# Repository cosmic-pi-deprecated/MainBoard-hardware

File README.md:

# MainBoard-hardware
Mainboard for Arduino DUE based versions

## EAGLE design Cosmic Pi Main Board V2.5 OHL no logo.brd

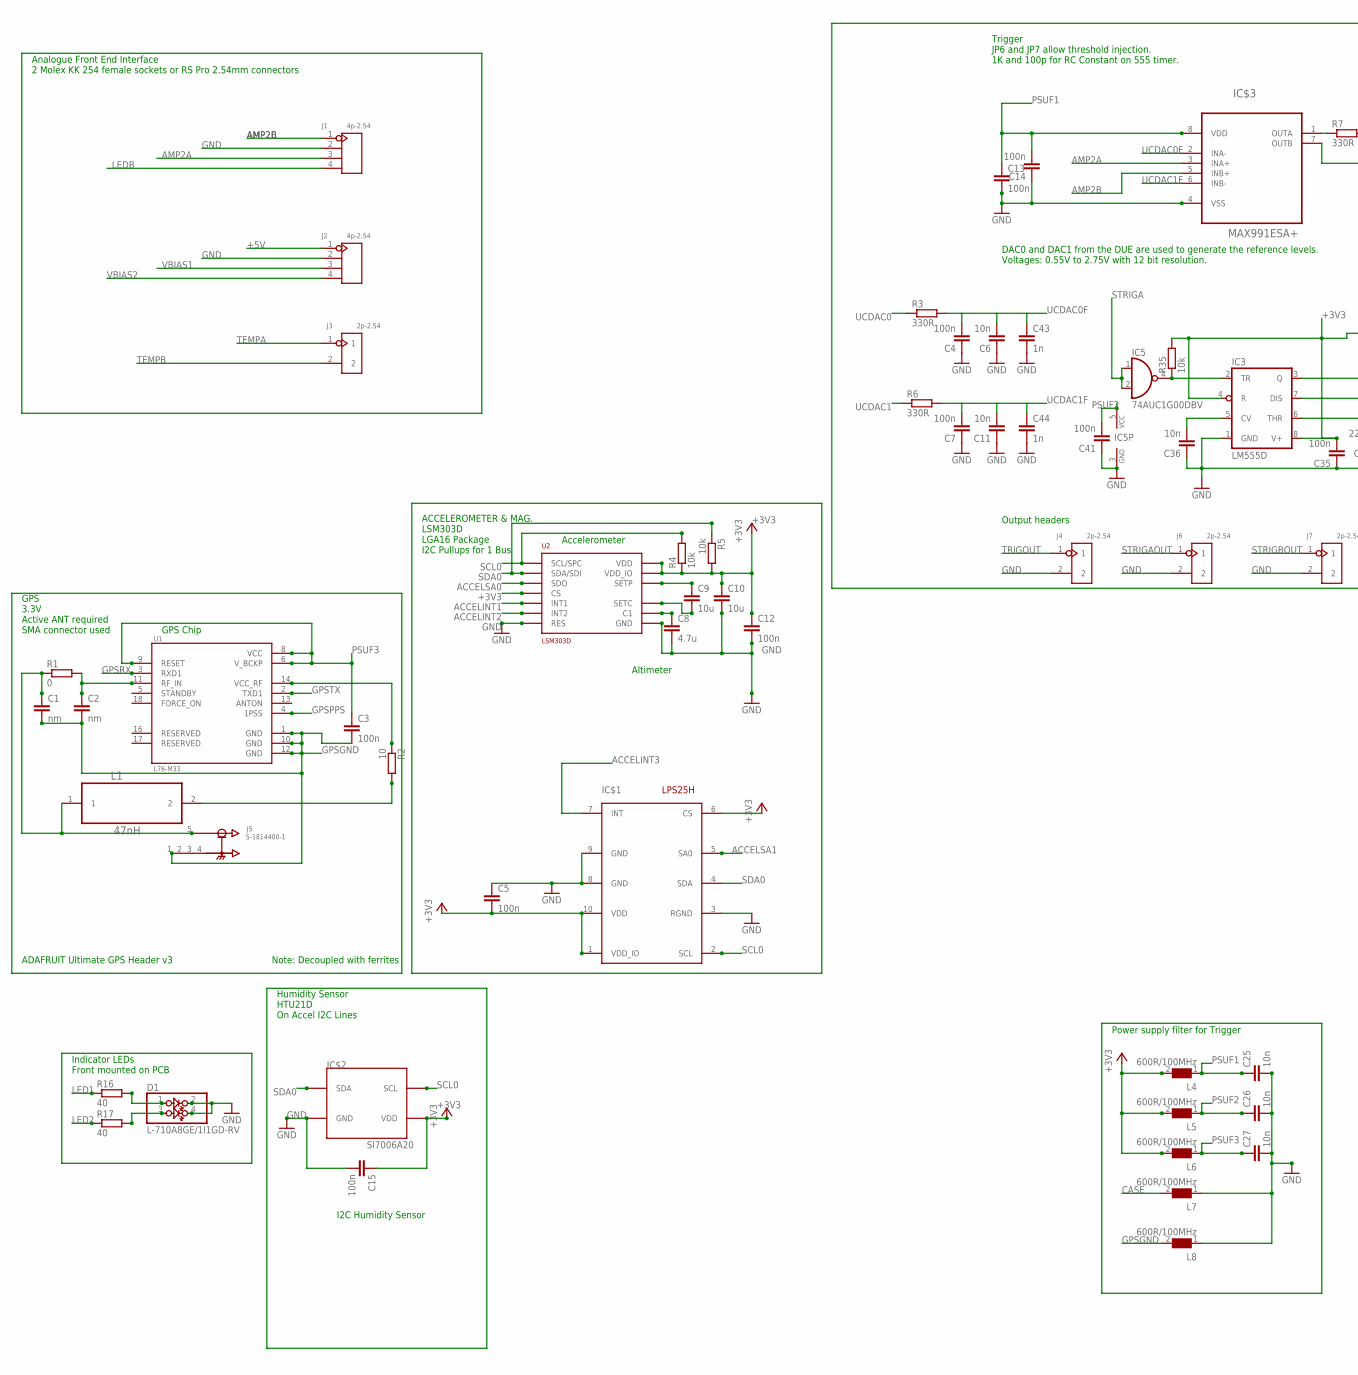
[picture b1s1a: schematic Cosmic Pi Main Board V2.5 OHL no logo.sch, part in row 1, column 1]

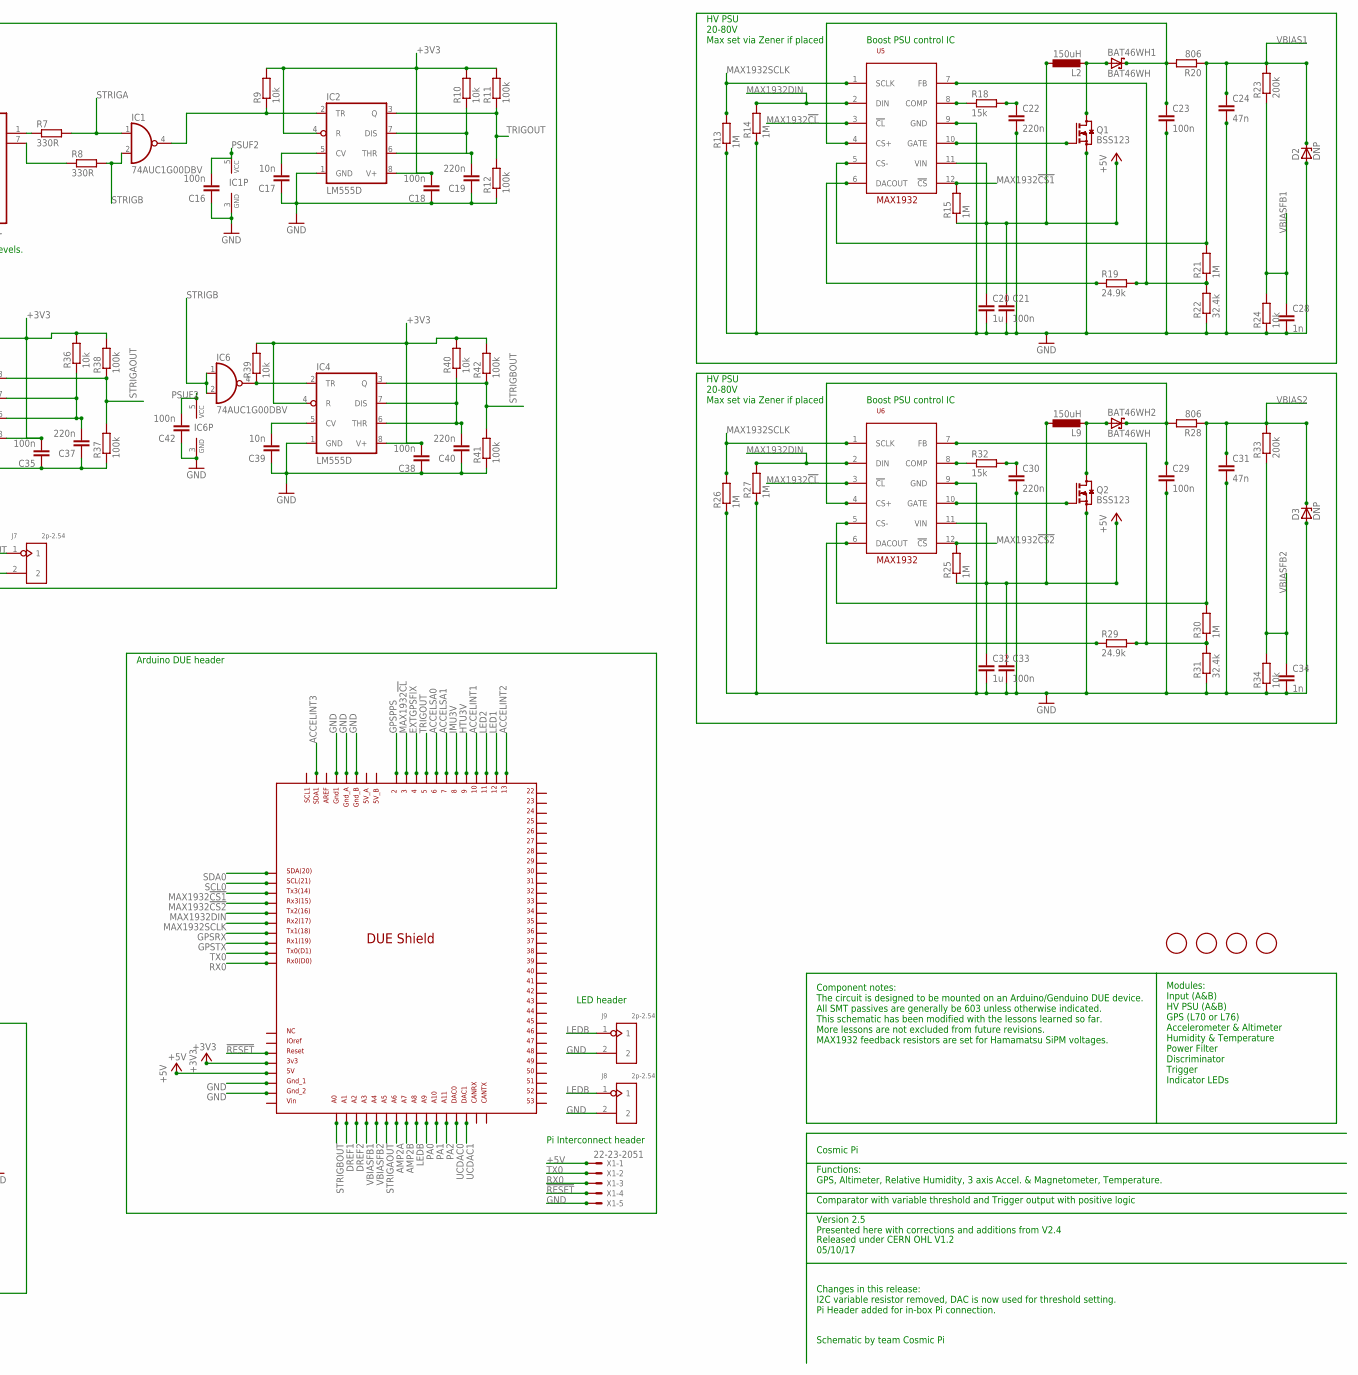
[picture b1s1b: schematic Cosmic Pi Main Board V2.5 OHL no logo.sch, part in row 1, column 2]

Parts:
BAT46WH1, BAT46WH2: BAT46WH; SOD123F
C1, C2: nm; C0603
C3, C4, C5, C7, C12, C13, C14, C15, C16, C18, C21, C23, C29, C33, C35, C38, C41, C42: 100n; C0603
C6, C11, C17, C25, C26, C27, C36, C39: 10n; C0603
C8: 4.7u; C0603
C9, C10: 10u; C0603
C19, C22, C30, C37, C40: 220n; C0603
C20, C32: 1u; C0603
C24, C31: 47n; C0603
C28, C34, C43, C44: 1n; C0603
D1: L-710A8GE/1I1GD-RV; 2X02
D2, D3: DNP; SOT23
DUE1: DUE(NORMAL)
IC1, IC5, IC6: 74AUC1G00DBV; SOT23-5
IC2, IC3, IC4: LM555D; SO08
IC$1: LPS25H
IC$2: SI7006A20; 3X3DFN
IC$3: MAX991ESA+; SOIC-8
J1, J2: 4p-2.54; H4-2.54
J3, J4, J6, J7, J8, J9: 2p-2.54; H2-2.54
J5: 5-1814400-1; TE_5-1814400-1
L1: 47nH; INDC1608X90N
L2, L9: 150uH; L1812
L4, L5, L6, L7, L8: 600R/100MHz; 1206
Q1, Q2: BSS123; SOT23
R1: 0; R0603
R2: 10; R0603
R3, R6, R7, R8: 330R; R0603
R4, R5, R9, R10, R24, R34, R35, R36, R39, R40: 10k; R0603
R11, R12, R37, R38, R41, R42: 100k; R0603
R13, R14, R15, R21, R25, R26, R27, R30: 1M; R0603
R16, R17: 40; R0603
R18, R32: 15k; R0603
R19, R29: 24.9k; R0603
R20, R28: 806; R0603
R22, R31: 32.4k; R0603
R23, R33: 200k; R0603
U1: L76-M33; CAPCAV110P970X1010X250-18N
U2: LSM303D; LGA16L
U5, U6: MAX1932; TQFN-12
U$1, U$2, U$3, U$4: FIDUCIAL; FIDUCIAL_1MM
X1: 22-23-2051

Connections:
!RESET: DUE1.RESET, X1.4
+3V3: C5.2, C10.1, C12.1, C15.1, C18.2, C35.2, C38.2, DUE1.3V3, IC2.4 (R), IC2.8 (V+), IC3.4 (R), IC3.8 (V+), IC4.4 (R), IC4.8 (V+), IC$1.1 (VDD_IO), IC$1.6 (CS), IC$1.10 (VDD), IC$2.P$5 (VDD), L4.2, L5.2, L6.2, R4.1, R5.2, R9.2, R10.2, R11.2, R35.2, R36.2, R38.2, R39.2, R40.2, R42.2, U2.P$1 (VDD_IO), U2.P$8 (CS), U2.P$14 (VDD)
+5V: C20.1, C21.1, C32.1, C33.1, DUE1.5V, J2.1, L2.1, L9.1, R15.1, R25.1, U5.11 (VIN), U6.11 (VIN), X1.1
ACCELINT1: DUE1.10, U2.P$11 (INT1)
ACCELINT2: DUE1.13, U2.P$9 (INT2)
ACCELINT3: DUE1.SDA1, IC$1.7 (INT)
ACCELSA0: DUE1.6, U2.P$7 (SDO)
ACCELSA1: DUE1.7, IC$1.5 (SA0)
AMP2A: DUE1.A6, IC$3.3 (INA+), J1.3
AMP2B: DUE1.A7, IC$3.5 (INB+), J1.1
CASE: L7.2
DREF1: DUE1.A1
DREF2: DUE1.A2
EXTGPSFIX: DUE1.4
GND: C4.1, C5.1, C6.1, C7.1, C8.2, C10.2, C11.1, C12.2, C13.2, C14.1, C15.2, C16.1, C17.1, C18.1, C19.1, C20.2, C21.2, C22.2, C23.2, C24.2, C25.2, C26.2, C27.2, C28.2, C29.2, C30.2, C31.2, C32.2, C33.2, C34.2, C35.1, C36.1, C37.1, C38.1, C39.1, C40.1, C41.1, C42.1, C43.2, C44.2, D1.2, D1.4, D2.1 (A), D3.1 (A), DUE1.GND1, DUE1.GND_1, DUE1.GND_2, DUE1.GND_A, DUE1.GND_B, IC1.3 (GND), IC2.1 (GND), IC3.1 (GND), IC4.1 (GND), IC5.3 (GND), IC6.3 (GND), IC$1.3 (RGND), IC$1.8 (GND), IC$1.9 (GND), IC$2.P$2 (GND), IC$3.4 (VSS), J1.2, J2.2, J4.2, J6.2, J7.2, J8.2, J9.2, L7.1, L8.1, Q1.2 (S), Q2.2 (S), R12.1, R13.1, R14.1, R22.1, R24.1, R26.1, R27.1, R31.1, R34.1, R37.1, R41.1, U2.P$5 (GND), U2.P$10 (RES), U2.P$12 (GND), U2.P$13 (GND), U2.P$16 (GND), U5.9 (GND), U6.9 (GND), X1.5
GPSGND: C1.2, C2.2, C3.2, J5.1 (GND), L8.2, U1.1 (GND), U1.10 (GND), U1.12 (GND)
GPSPPS: DUE1.2, U1.4 (1PSS)
GPSRX: DUE1.TX1, U1.3 (RXD1)
GPSTX: DUE1.RX1, U1.2 (TXD1)
HTU3V: DUE1.9
IMU3V: DUE1.8
LED1: DUE1.12, R16.1
LED2: DUE1.11, R17.1
LEDB: DUE1.A8, J1.4, J8.1, J9.1
MAX1932!CL: DUE1.3, U5.3 (!CL), U6.3 (!CL)
MAX1932!CS1: DUE1.TX3, R15.2, U5.12 (!CS)
MAX1932!CS2: DUE1.RX3, R25.2, U6.12 (!CS)
MAX1932DIN: DUE1.TX2, R14.2, R27.2, U5.2 (DIN), U6.2 (DIN)
MAX1932SCLK: DUE1.RX2, R13.2, R26.2, U5.1 (SCLK), U6.1 (SCLK)
unnamed: IC$3.1 (OUTA), R7.1
unnamed: IC$3.7 (OUTB), R8.1
unnamed: C17.2, IC2.5 (CV)
unnamed: C19.2, IC2.6 (THR), IC2.7 (DIS), R10.1
unnamed: C36.2, IC3.5 (CV)
unnamed: Q2.1 (G), U6.10 (GATE)
unnamed: BAT46WH2.2 (A), L9.2, Q2.3 (D)
unnamed: BAT46WH2.1 (K), C29.1, R28.2, U6.4 (CS+)
unnamed: R29.1, U6.6 (DACOUT)
unnamed: R32.1, U6.8 (COMP)
unnamed: C30.1, R32.2
unnamed: R29.2, R30.1, R31.2, U6.7 (FB)
unnamed: C37.2, IC3.6 (THR), IC3.7 (DIS), R36.1
unnamed: IC1.4 (O), IC2.2 (TR), R9.1
unnamed: Q1.1 (G), U5.10 (GATE)
unnamed: C39.2, IC4.5 (CV)
unnamed: C40.2, IC4.6 (THR), IC4.7 (DIS), R40.1
unnamed: IC4.2 (TR), IC6.4 (O), R39.1
unnamed: IC3.2 (TR), IC5.4 (O), R35.1
unnamed: BAT46WH1.2 (A), L2.2, Q1.3 (D)
unnamed: BAT46WH1.1 (K), C23.1, R20.2, U5.4 (CS+)
unnamed: R19.2, R21.1, R22.2, U5.7 (FB)
unnamed: C1.1, J5.5 (SIG), L1.1, R1.1
unnamed: R19.1, U5.6 (DACOUT)
unnamed: R18.1, U5.8 (COMP)
unnamed: C22.1, R18.2
unnamed: C9.1, U2.P$3 (SETP)
unnamed: C9.2, U2.P$2 (SETC)
unnamed: C8.1, U2.P$15 (C1)
unnamed: L1.2, R2.2
unnamed: R2.1, U1.14 (VCC_RF)
unnamed: C2.1, R1.2, U1.11 (RF_IN)
unnamed: D1.1, R16.2
unnamed: D1.3, R17.2
PA0: DUE1.A9
PA1: DUE1.A10
PA2: DUE1.A11
PSUF1: C13.1, C14.2, C25.1, IC$3.8 (VDD), L4.1
PSUF2: C16.2, C26.1, C41.2, C42.2, IC1.5 (VCC), IC5.5 (VCC), IC6.5 (VCC), L5.1
PSUF3: C3.1, C27.1, L6.1, U1.6 (V_BCKP), U1.8 (VCC), U1.9 (RESET)
RX0: DUE1.RX0, X1.3
SCL0: DUE1.SCL, IC$1.2 (SCL), IC$2.P$6 (SCL), R4.2, U2.P$4 (SCL/SPC)
SDA0: DUE1.SDA, IC$1.4 (SDA), IC$2.P$1 (SDA), R5.1, U2.P$6 (SDA/SDI)
STRIGA: IC1.1 (I0), IC5.1 (I0), IC5.2 (I1), R7.2
STRIGAOUT: DUE1.A5, IC3.3 (Q), J6.1, R37.2, R38.1
STRIGB: IC1.2 (I1), IC6.1 (I0), IC6.2 (I1), R8.2
STRIGBOUT: DUE1.A0, IC4.3 (Q), J7.1, R41.2, R42.1
TEMPA: J3.1
TEMPB: J3.2
TRIGOUT: DUE1.5, IC2.3 (Q), J4.1, R11.1, R12.2
TX0: DUE1.TX0, X1.2
UCDAC0: DUE1.DAC0, R3.1
UCDAC0F: C4.2, C6.2, C43.1, IC$3.2 (INA-), R3.2
UCDAC1: DUE1.DAC1, R6.1
UCDAC1F: C7.2, C11.2, C44.1, IC$3.6 (INB-), R6.2
VBIAS1: C24.1, D2.3 (C), J2.3, R20.1, R21.2, R23.2, U5.5 (CS-)
VBIAS2: C31.1, D3.3 (C), J2.4, R28.1, R30.2, R33.2, U6.5 (CS-)
VBIASFB1: C28.1, DUE1.A3, R23.1, R24.2
VBIASFB2: C34.1, DUE1.A4, R33.1, R34.2

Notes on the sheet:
Cosmic Pi
Functions: GPS, Altimeter, Relative Humidity, 3 axis Accel. & Magnetometer, Temperature.
Comparator with variable threshold and Trigger output with positive logic
Version 2.5 Presented here with corrections and additions from V2.4
Released under CERN OHL V1.2 05/10/17
Schematic by team Cosmic Pi
HV PSU 20-80V Max set via Zener if placed
GPS 3.3V Active ANT required SMA connector used
ACCELEROMETER & MAG. LSM303D LGA16 Package I2C Pullups for 1 Bus
ADAFRUIT Ultimate GPS Header v3
Trigger JP6 and JP7 allow threshold injection. 1K and 100p for RC Constant on 555 timer.
Power supply filter for Trigger
Arduino DUE header
Humidity Sensor HTU21D On Accel I2C Lines
Indicator LEDs Front mounted on PCB
Modules: Input (A&B) HV PSU (A&B) GPS (L70 or L76) Accelerometer & Altimeter Humidity & Temperature Power Filter Discriminator Trigger Indicator LEDs
Accelerometer
Altimeter
GPS Chip
I2C Humidity Sensor
Boost PSU control IC
Component notes: The circuit is designed to be mounted on an Arduino/Genduino DUE device. All SMT passives are generally be 603 unless otherwise indicated. This schematic has been modified with the lessons learned so far. More lessons are not excluded from future revisions. MAX1932 feedback resisto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
Analogue Front End Interface 2 Molex KK 254 female sockets or RS Pro 2.54mm connectors
Note: Decoupled with ferrites
Changes in this release: I2C variable resistor removed, DAC is now used for threshold setting. Pi Header added for in-box Pi connection.
DAC0 and DAC1 from the DUE are used to generate the reference levels. Voltages: 0.55V to 2.75V with 12 bit resolution.
Pi Interconnect header
Output headers
LED header

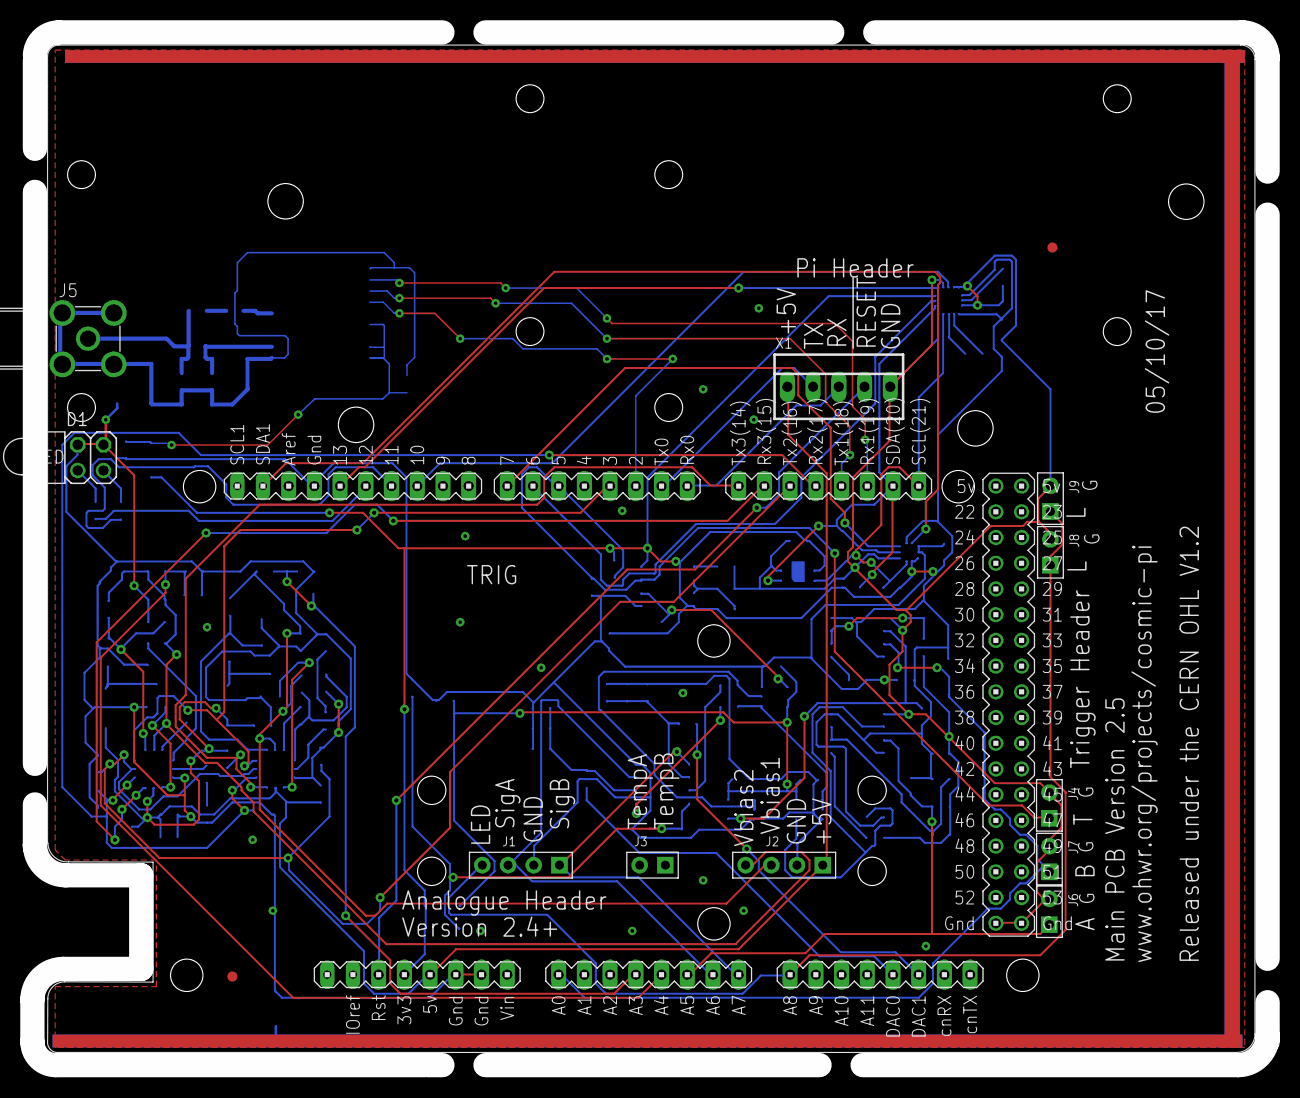
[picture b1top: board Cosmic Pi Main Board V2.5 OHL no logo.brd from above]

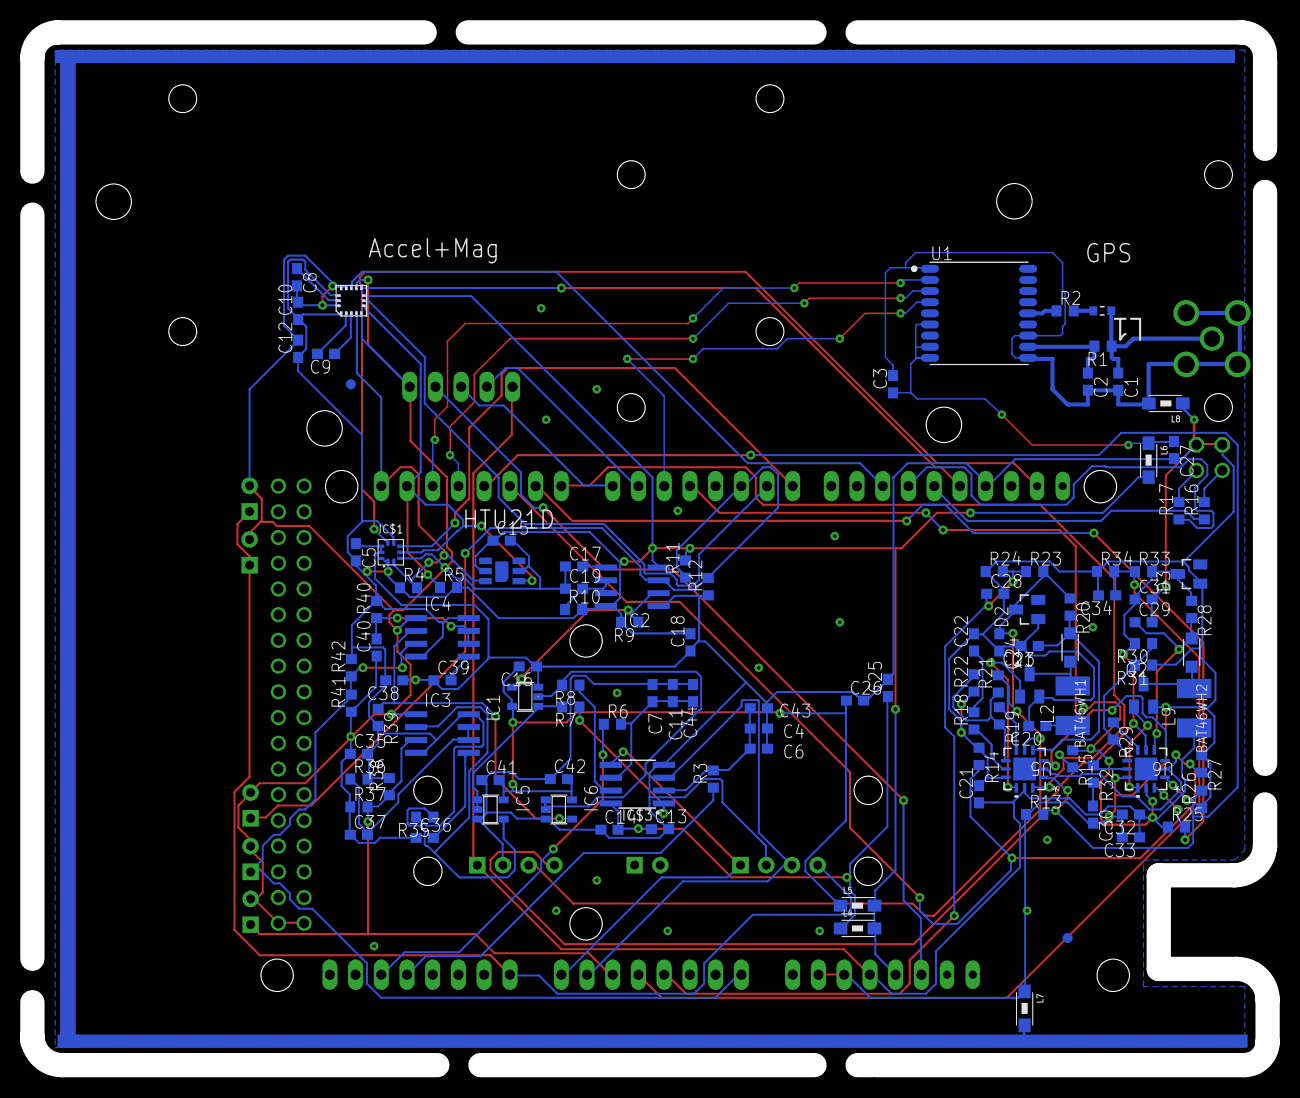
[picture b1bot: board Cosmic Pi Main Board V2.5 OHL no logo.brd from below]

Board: 2 copper layers, 122.0 x 102.0 mm, 129 parts (115 on the bottom side), 77 nets.

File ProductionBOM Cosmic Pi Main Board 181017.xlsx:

Qty | Value | Parts | Package | Tolerance | Wattage | Voltage Rating | Manufacturer | MPN | Description | Device | Side | Mounting
1 | 22-23-2051 | 22-23-2051 | H5-2.54 |  |  |  | Harwin | M20-9990546 | 5 Pin 2.54mm pitch male header |  | Top | TH
1 | 0 | R1 | R0603 | 0.01 | 0.1W |  |  |  | RESISTOR, European symbol | R-EU_R0603 | Bottom | SMD
1 | 10 | R2 | R0603 | 0.01 | 0.1W |  |  |  | RESISTOR, European symbol | R-EU_R0603 | Bottom | SMD
6 | 100k | R11, R12, R37, R38, R41, R42 | R0603 | 0.01 | 0.1W |  |  |  | RESISTOR, European symbol | R-EU_R0603 | Bottom | SMD
18 | 100n | C3, C4, C5, C7, C12, C13, C14, C15, C16, C18, C21, C23, C29, C33, C35, C38, C41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 | C0603 | 0.1 |  | 100 |  |  | CAPACITOR, European symbol | C-EUC0603 | Bottom | SMD
10 | 10k | R4, R5, R9, R10, R24, R34, R35, R36, R39, R40 | R0603 | 0.01 | 0.1W |  |  |  | RESISTOR, European symbol | R-EU_R0603 | Bottom | SMD
8 | 10n | C6, C11, C17, C25, C26, C27, C36, C39 | C0603 | 0.1 |  | 10 |  |  | CAPACITOR, European symbol | C-EUC0603 | Bottom | SMD
2 | 10u | C9, C10 | C0603 | 0.1 |  |  |  |  | CAPACITOR, European symbol | C-EUC0603 | Bottom | SMD
2 | 150uH | L2, L9 | L1812 |  |  |  | Bourns | CM453232-151KL | INDUCTOR, European symbol | L-EUL1812 | Bottom | SMD
2 | 15k | R18, R32 | R0603 | 0.01 | 0.1W |  |  |  | RESISTOR, European symbol | R-EU_R0603 | Bottom | SMD
8 | 1M | R13, R14, R15, R21, R25, R26, R27, R30 | R0603 | 0.01 | 1/16W |  |  |  | RESISTOR, European symbol | R-EU_R0603 | Bottom | SMD
4 | 1n | C28, C34, C43, C44 | C0603 | 0.1 |  | 10 |  |  | CAPACITOR, European symbol | C-EUC0603 | Bottom | SMD
2 | 1u | C20, C32 | C0603 | -20/+80% |  | 10 |  |  | CAPACITOR, European symbol | C-EUC0603 | Bottom | SMD
2 | 200k | R23, R33 | R0603 | 0.05 | 1/16W |  |  |  | RESISTOR, European symbol | R-EU_R0603 | Bottom | SMD
5 | 220n | C19, C22, C30, C37, C40 | C0603 | 0.1 |  | 10 |  |  | CAPACITOR, European symbol | C-EUC0603 | Bottom | SMD
2 | 24.9k | R19, R29 | R0603 | 0.01 | 0.2W |  |  | ERJP03F24R9V | RESISTOR, European symbol | R-EU_R0603 | Bottom | SMD
2 | 32.4k | R22, R31 | R0603 | 0.01 | 0.1W |  |  | ERJ3EKF3242V | RESISTOR, European symbol | R-EU_R0603 | Bottom | SMD
4 | 330R | R3, R6, R7, R8 | R0603 | 0.05 | 1/16W |  |  |  | RESISTOR, European symbol | R-EU_R0603 | Bottom | SMD
1 | 4.7u | C8 | C0603 | 0.1 |  | 10 |  |  | CAPACITOR, European symbol | C-EUC0603 | Bottom | SMD
2 | 40 | R16, R17 | R0603 | 0.05 | 1/16W |  |  | ERJ3EKF40R2V | RESISTOR, European symbol | R-EU_R0603 | Bottom | SMD
2 | 47n | C24, C31 | C0603 | 0.1 |  | 100 |  | C1608X7S2A473K080AB | CAPACITOR, European symbol | C-EUC0603 | Bottom | SMD
1 | 47nH | L1 | INDC1608X90N |  |  |  | EPCOS | B82496C3470J000 | INDUCTOR, 47NH 270MA 5% | B82496C3470J | Bottom | SMD
2 | 4p-2.54 | J1, J2 | H4-2.54 |  |  |  | Harwin | M20-7820446 | 320030017 | DIP-BLACK-FEMALE-HEADER-VERT(4P-2.54) | Top | SMD
1 | 5-1814400-1 | J5 | TE_5-1814400-1 |  |  |  | TE Connectivity | 5-1814400-1 | Conn SMA RCP 0Hz to 3GHz 50Ohm Solder RA Thru-Hole Gold Over Nickel Over Copper | 5-1814400-1 | Top | TH
5 | 600R/100MHz | L4, L5, L6, L7, L8 | 1206 |  |  |  | Wurth | 74279218 | SMD EMI Suppression Ferrite Beads WE-CBF | WE-CBF-74279218_1206 | Bottom | SMD
3 | 74AUC1G00DBV | IC1, IC5, IC6 | SOT23-5 |  |  |  | Texas Instruments | SN74AHCT1G00DBVR | 2-input NAND gate | 74AUC1G00DBV | Bottom | SMD
2 | 806 | R20, R28 | R0603 | 0.01 | 0.1W |  | Farnell | 2670898 | RESISTOR, European symbol | R-EU_R0603 | Bottom | SMD
2 | BAT46WH | BAT46WH1, BAT46WH2 | SOD123F |  |  |  | Nexperia | BAT46WH | Single Schottky barrier diodeSingle planar Schottky barrier diode with an integ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 | BAT46WH | Bottom | SMD
2 | BSS123 | Q1, Q2 | SOT23 |  |  |  | Diodes Zetex | BSS123-7-F | N-CHANNEL MOS FET | BSS123 | Bottom | SMD
1 | DUE(NORMAL) | DUE1 | DUE(NORMAL) |  |  |  | Harwin | 5 of M20-9990845, 1 of M20-9991046 | Note - this 'part is actually 6 sets of pin headers for the Arduino DUE. The 40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 | DUE(NORMAL) | Bottom | TH
1 | L-710A8GE/1I1GD-RV | D1 | 2X02 |  |  |  | Kingbright | L-710A8GE/1I1GD-RV | PIN HEADER | KINGBRITET1 | Top | TH
1 | L76-M33 | U1 | CAPCAV110P970X1010X250-18N |  |  |  | Quectel | L76-M33 | GPS Receiver 1575.42MHz 2.5V/3.3V 18-Pin | L76-M33 | Bottom | SMD
3 | LM555D | IC2, IC3, IC4 | SO08 |  |  |  | Texas Instruments | TLC555ID | TIMER | LM555D | Bottom | SMD
1 | LPS25H | IC$1 | LPS25H |  |  |  | ST Micro | LPS25HBTR | ST-Micro Piezoresistive pressure sensor | LPS25H | Bottom | SMD
1 | LSM303D | U2 | LGA16L |  |  |  | ST Micro | LSM303DTR |  | LSM303D | Bottom | SMD
2 | MAX1932 | U5, U6 | TQFN-12 |  |  |  | Maxim | MAX1932ETC+ |  | MAX1932 | Bottom | SMD
1 | MAX991ESA+ | IC$3 | SOIC-8 |  |  |  | Maxim | MAX991ESA+ |  | MAX991ESA+ | Bottom | SMD
1 | SI7006A20 | IC$2 | 3X3DFN |  |  |  | Silicon Labs | Si7006-A20-IM |  | SI7006A20 | Bottom | SMD
120 | Total
91 | SMD
11 | TH
4 | Packages with concealed pads
84 | Passives

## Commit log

2017-09-18 Design files for intermediate main board (still uses DUE)
2017-10-26 Updated V2.5 with pi mini-header
2017-10-26 Added license conditions
    CERN OHL V1.2
2017-11-20 Assembly guide - also covers V2.5 Analogue PCB

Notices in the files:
Cosmic Pi Main Board V2.5 OHL no logo.brd:
Released under the CERN OHL V1.2
